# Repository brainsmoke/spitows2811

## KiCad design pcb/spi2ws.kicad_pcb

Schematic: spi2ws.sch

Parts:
C1: C
CON1: AVR-ISP-6-NEW; AVR-ISP-6
IC1: ATTINY85-S; SO8-200
P1, P3, P4, P5, P6: CONN_1

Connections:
GND: C1.2, CON1.6, IC1.4 (GND), P3.1
unnamed: CON1.4, IC1.5 (PB0(MOSI/DI/SDA/AIN0/OC0A/OC1A/AREF/PCI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), P4.1
unnamed: IC1.3 (PB4(XTAL2/CLKO/OC1B/ADC2/PCINT4)), P6.1
unnamed: CON1.1, IC1.6 (PB1(MISO/DO/AIN1/OC0B/OC1A/PCINT1))
unnamed: CON1.3, IC1.7 (PB2(SCK/USCK/SCL/T0/INT0/ADC1/PCINT2)), P5.1
unnamed: CON1.5, IC1.1 (PB5(~RESET~/dW/ADC0/PCINT5))
VCC: C1.1, CON1.2, IC1.8 (VCC), P1.1

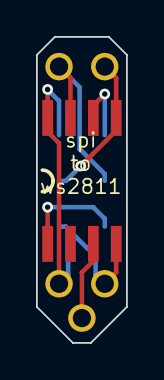
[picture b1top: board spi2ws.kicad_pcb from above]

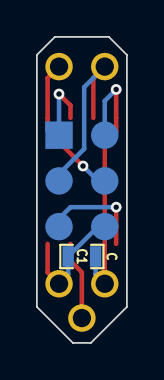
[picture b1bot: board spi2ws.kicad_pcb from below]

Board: 2 copper layers, 5.0 x 17.0 mm, 8 parts (2 on the bottom side), 7 nets.

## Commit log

2015-04-17 SPI to WS2811/WS2812/WS2812b protocol translator
2015-04-21 untested fix for untriggered bug
2015-04-22 add some comments
2015-04-22 clarify comments
2015-04-22 remove 8 bit limit on pre-transmit cache size (untested)
2015-04-25 fixed cycle count comments
2015-04-25 fix comment
